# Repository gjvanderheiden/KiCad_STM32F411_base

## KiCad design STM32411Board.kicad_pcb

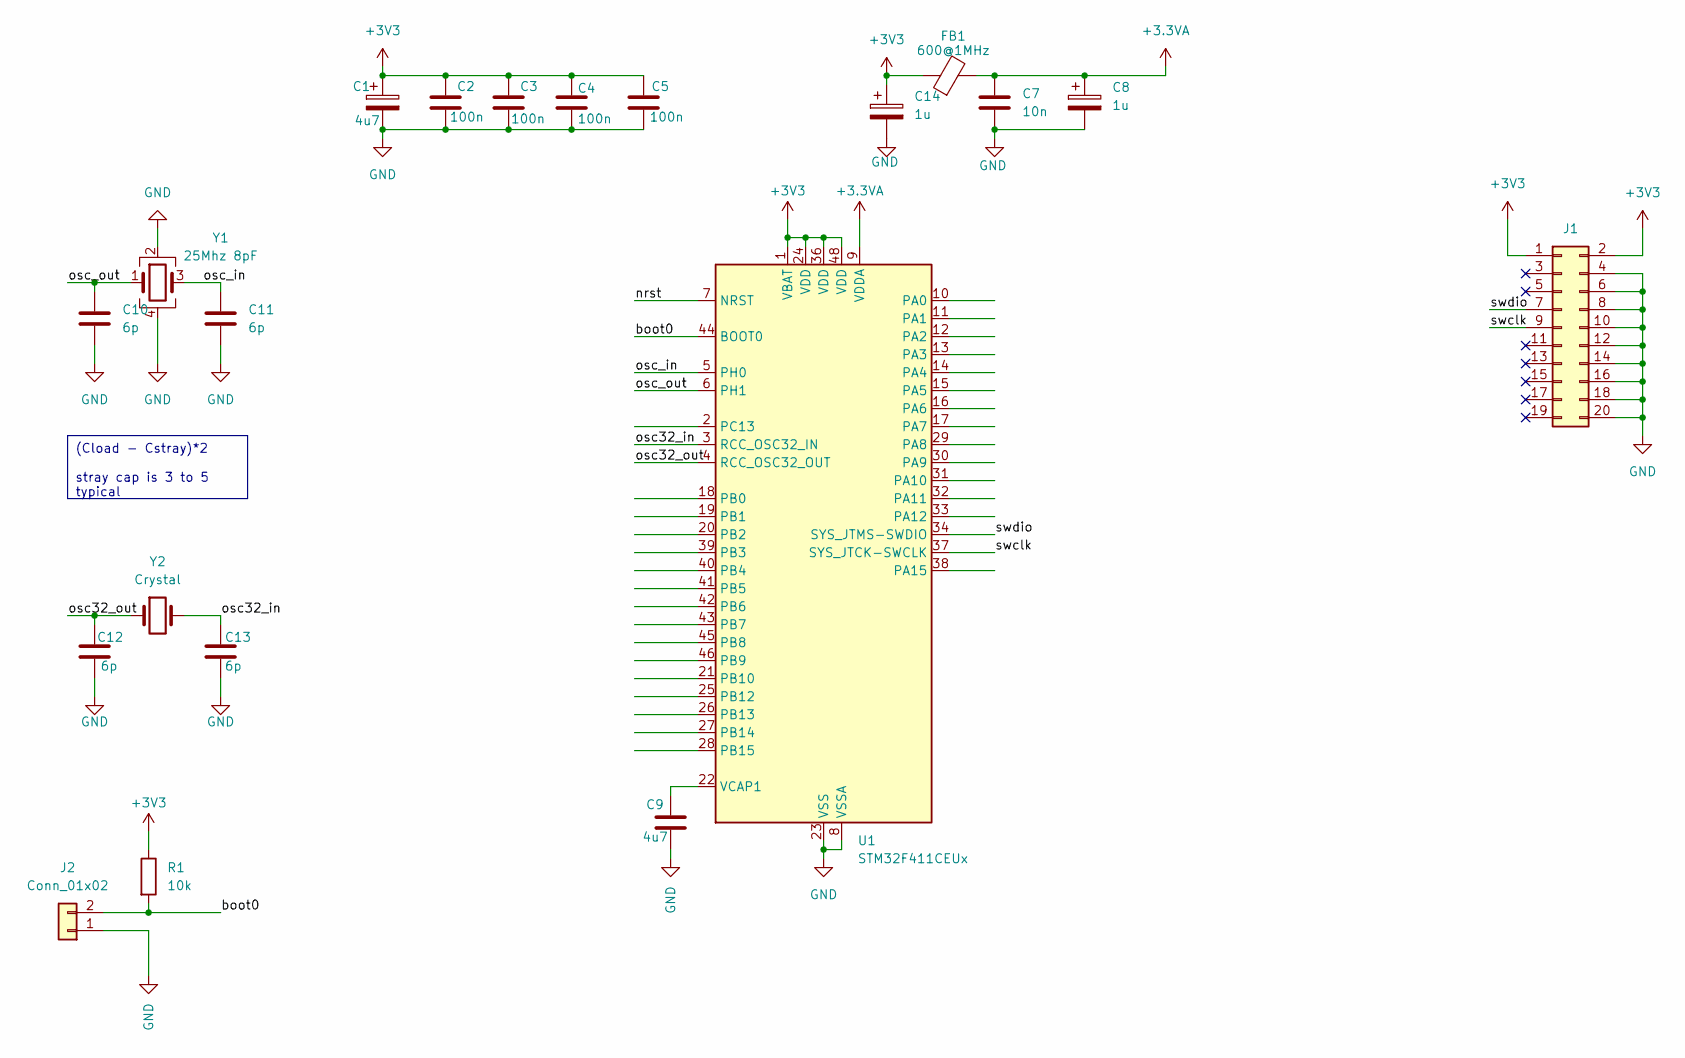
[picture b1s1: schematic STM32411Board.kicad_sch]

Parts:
C1, C9: 4u7; C_0603_1608Metric
C2, C3, C4, C5: 100n; C_0603_1608Metric
C7: 10n; C_0603_1608Metric
C8, C14: 1u; C_0603_1608Metric
C10, C11, C12, C13: 6p; C_0603_1608Metric
FB1: 600@1MHz; Fuse_0603_1608Metric_Pad1.05x0.95mm_HandSolder
J1: Conn_02x10_Odd_Even; IDC-Header_2x10_P2.54mm_Vertical
J2: Conn_01x02; PinHeader_1x02_P2.54mm_Vertical
R1: 10k; R_0805_2012Metric
U1: STM32F411CEUx; QFN-48-1EP_7x7mm_P0.5mm_EP5.6x5.6mm
Y1: 25Mhz 8pF; Crystal_SMD_3225-4Pin_3.2x2.5mm
Y2: Crystal; Crystal_SMD_3215-2Pin_3.2x1.5mm

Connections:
+3.3VA: C7.1, C8.1, FB1.2, U1.9 (VDDA)
+3V3: C1.1, C2.1, C3.1, C4.1, C5.1, C14.1, FB1.1, J1.1, J1.2, R1.1, U1.1 (VBAT), U1.24 (VDD), U1.36 (VDD), U1.48 (VDD)
/boot0: J2.2, R1.2, U1.44 (BOOT0)
/nrst: U1.7 (NRST)
/osc32_in: C13.1, U1.3 (RCC_OSC32_IN), Y2.2
/osc32_out: C12.1, U1.4 (RCC_OSC32_OUT), Y2.1
/osc_in: C11.1, U1.5 (PH0), Y1.3
/osc_out: C10.1, U1.6 (PH1), Y1.1
/swclk: J1.9, U1.37 (SYS_JTCK-SWCLK)
/swdio: J1.7, U1.34 (SYS_JTMS-SWDIO)
GND: C1.2, C2.2, C3.2, C4.2, C5.2, C7.2, C8.2, C9.1, C10.2, C11.2, C12.2, C13.2, C14.2, J1.4, J1.6, J1.8, J1.10, J1.12, J1.14, J1.16, J1.18, J1.20, J2.1, U1.8 (VSSA), U1.23 (VSS), U1.35 (VSS), U1.47 (VSS), U1.49 (VSS), Y1.2, Y1.4
unnamed: C9.2, U1.22 (VCAP1)

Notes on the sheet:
(Cload - Cstray)*2 stray cap is 3 to 5 typical

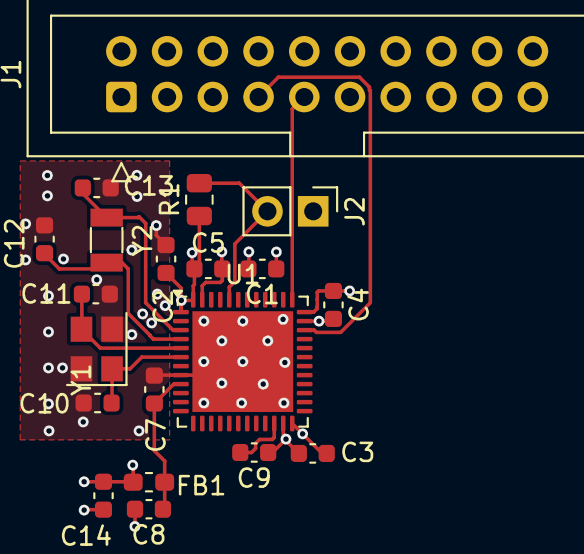
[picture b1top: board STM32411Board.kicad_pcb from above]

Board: 4 copper layers, 20 parts (0 on the bottom side), 11 nets.

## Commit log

2025-02-01 init commit
2025-02-05 updated crystal
